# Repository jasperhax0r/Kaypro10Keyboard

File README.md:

# Kaypro 10 Replacement Keyboard

A modern replacement keyboard for the Kaypro 10 that fits the original case, using Cherry MX-style switches and a Raspberry Pi Pico running MicroPython to emulate the original 300 baud serial keyboard interface.

*KiCad 3D render of the PCB*

*Prototype board installed and working*

---

## Overview

The original Kaypro 10 keyboard is increasingly difficult to find in working condition. This project provides a drop-in replacement that:

- Fits the original Kaypro 10 keyboard case with no modifications
- Uses modern Cherry MX-style mechanical switches
- Communicates over the Kaypro's original 300 baud serial keyboard interface
- Is driven by a Raspberry Pi Pico running MicroPython
- Includes a 3D printed switch support plate (no metal plate in this design)

---

## Repository Contents

All files are in the root of the repository.

| File | Description |
|------|-------------|
| `*.kicad_pro`, `*.kicad_sch`, `*.kicad_pcb`, etc. | KiCad 10 schematic and PCB design files |
| `KayproKeyboard.zip` | Generated Gerber/manufacturing files, ready to send to a PCB fab |
| `KayproKeyboard.png` | KiCad 3D render of the board |
| `keyboard support.stl` | 3D printable switch support plate |
| `main.py` | MicroPython firmware for the Raspberry Pi Pico |
| `PXL_20260531_222427528.jpg` | Photo of the working prototype |

---

## Bill of Materials

| Qty | Component | Notes |
|-----|-----------|-------|
| 76 | 1N4148 diode | One per switch, for key matrix decoding |
| 76 | Cherry MX-style switches | One per key position |
| — | PCB-mount stabilizers | Required for larger keys (spacebar, shift, enter, etc.) — quantity depends on layout |
| 1 | Waveshare BS138 4-channel bidirectional level shifter module | 3.3V ↔ 5V logic level conversion |
| 1 | Passive buzzer/speaker | Key click feedback |
| 1 | LED (single, any color) | Status indicator |
| 1 | 330Ω resistor | LED current limiting |
| 1 | 47kΩ resistor | Pull-up/pull-down for serial line |
| 1 | Protection diode | 5V input protection for the Pico |
| 1 | Raspberry Pi Pico | Main controller (standard Pico, not Pico W) |
| 1 | 6-pin horizontal header | Serial interface connector to Kaypro mainboard |

> **Note:** Use 1N4148 diodes (or equivalent) for the key matrix. One diode is required per switch to prevent ghosting.

---

## PCB Manufacturing

The file `KayproKeyboard.zip` contains all Gerber files needed for fabrication. It can be uploaded directly to most PCB manufacturers (JLCPCB, PCBWay, OSHPark, etc.) without modification.

Recommended specs:
- **Layers:** 2
- **Thickness:** 1.6mm
- **Surface finish:** HASL or ENIG

---

## 3D Printed Support

Because this design does not use a metal switch plate, a 3D printed support structure (`keyboard support.stl`) is included to provide rigidity and hold the switches in alignment during soldering and use.

Print in PLA or PETG at 0.2mm layer height with at least 20% infill. No supports should be needed.

---

## Firmware

The Pico runs MicroPython. Copy `main.py` to the Pico's root filesystem and it will start automatically on boot.

### Flashing the Pico

1. Hold the BOOTSEL button and connect the Pico to your computer via USB.
2. It will appear as a USB mass storage device (`RPI-RP2`).
3. Flash the latest [MicroPython UF2](https://micropython.org/download/rp2-pico/) by dragging it onto the drive.
4. Once rebooted, use a tool like [Thonny](https://thonny.org/) or `mpremote` to copy `main.py` to the Pico:
   ```
   mpremote cp main.py :main.py
   ```

The firmware reads the key matrix, debounces inputs, and outputs the correct character codes over the serial interface at 300 baud to match the Kaypro's original keyboard protocol.

---

## Connector Pinout

The keyboard connects to the Kaypro 10 mainboard via a 6-pin horizontal header. Pinout, numbered left to right:

| Pin | Signal | Description |
|-----|--------|-------------|
| 1 | 5V | Power from Kaypro mainboard |
| 2 | TX | Serial data out — keyboard → Kaypro, 300 baud |
| 3 | GND | Ground |
| 4 | GND | Ground |
| 5 | — | Missing/keyed pin (no connection) |
| 6 | RX | Serial data in — Kaypro → keyboard, 300 baud |

> ⚠️ **Important:** This pinout was determined from an **1983-spec Kaypro 10**. It may not be universal across all Kaypro models or revisions. Verify against your own machine before connecting. The protection diode on the 5V input and the BS138 level shifter are strongly recommended to avoid damaging the Pico.

The BS138 level shifter module handles 3.3V Pico ↔ 5V Kaypro logic translation on the TX and RX lines.

---

## Design Files

Schematics and PCB layout were created in **KiCad 10**. The KiCad project files are in the root directory and can be opened and modified freely.

---

## License

This project is open source. Schematics, PCB files, firmware, and mechanical files are provided as-is for personal and educational use.

Contributions, improvements, and ports to other Kaypro models are welcome — open a PR or issue!

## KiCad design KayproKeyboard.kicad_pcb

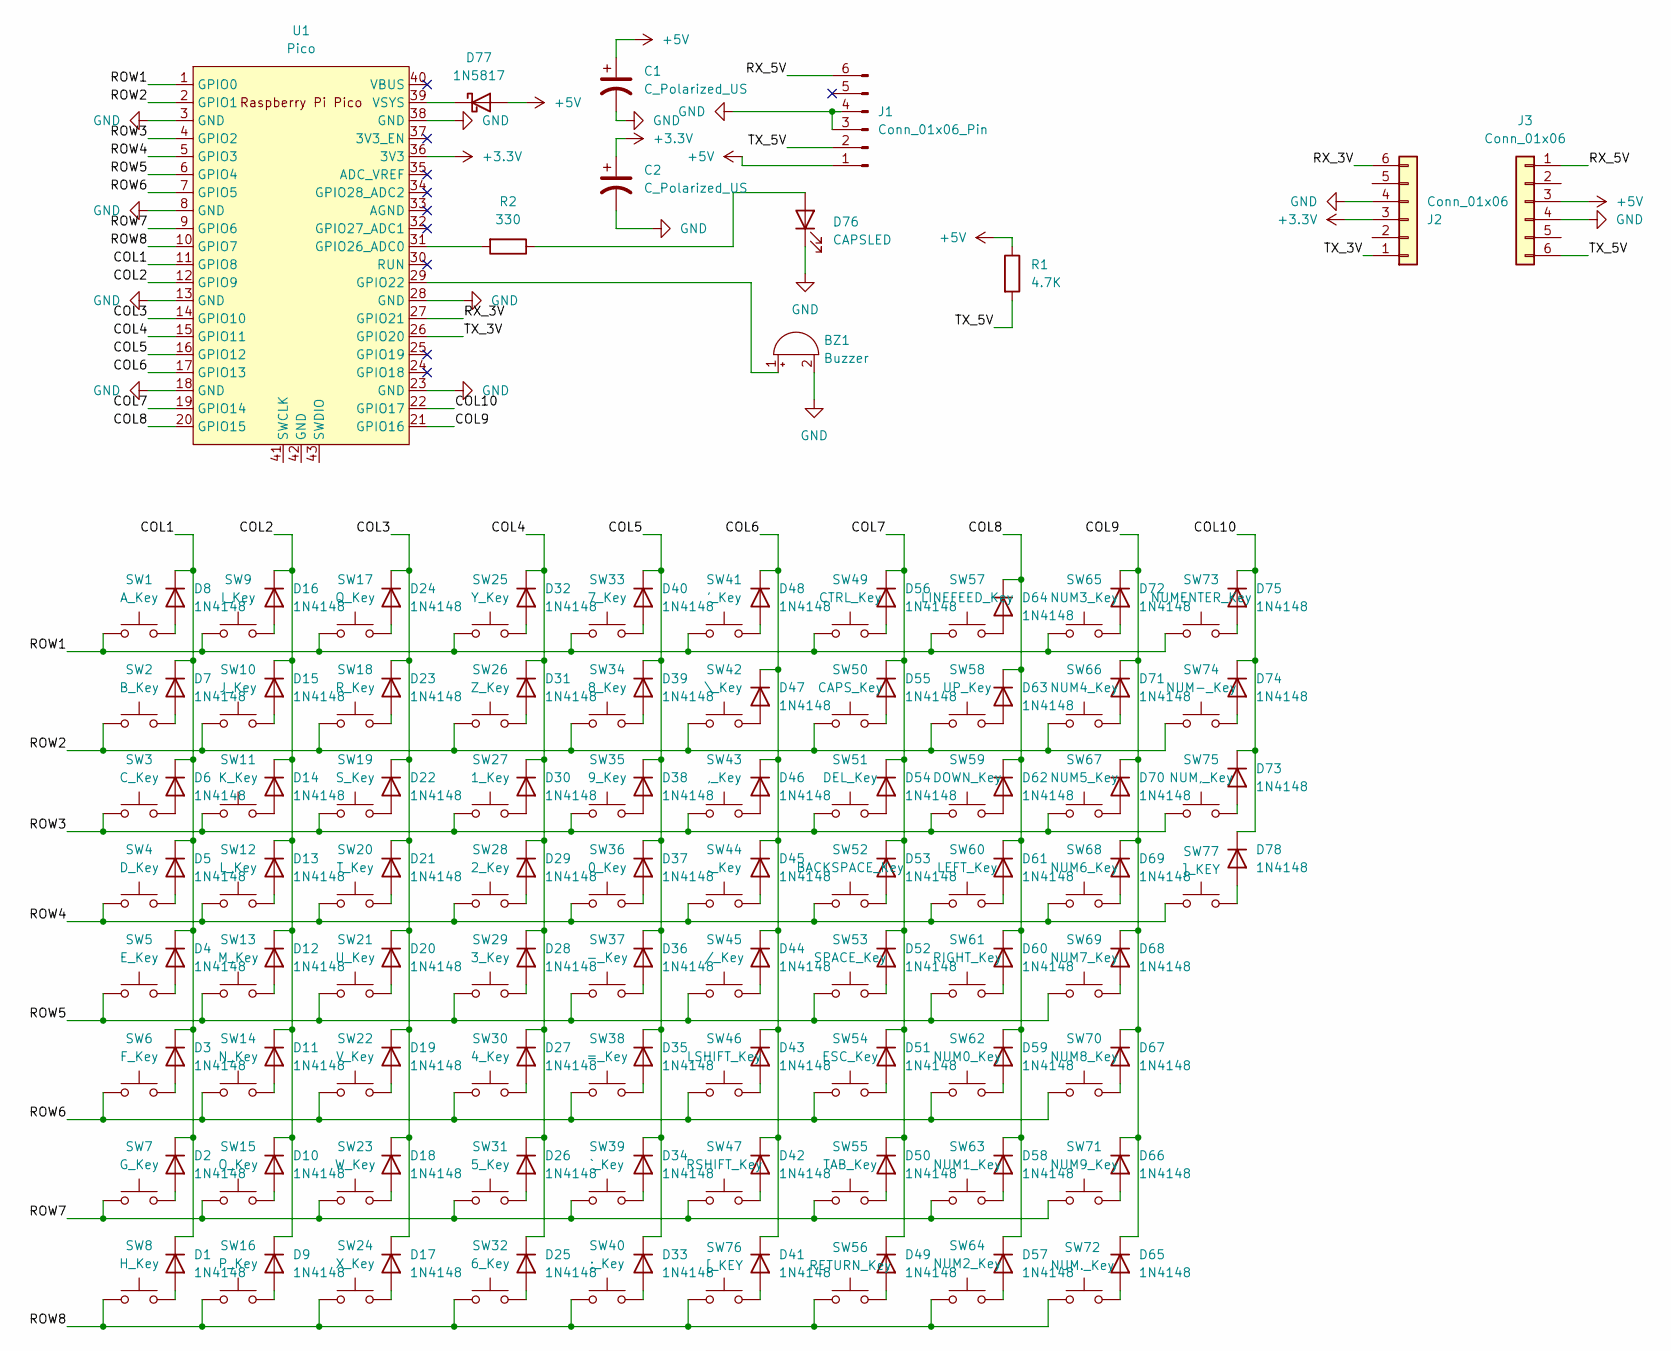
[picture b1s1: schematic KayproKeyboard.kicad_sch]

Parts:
BZ1: Buzzer; Buzzer_12x9.5RM7.6
C1, C2: C_Polarized_US; CP_Radial_D6.3mm_P2.50mm
D1, D2, D3, D4, D5, D6, D7, D8, D9, D10, D11, D12, D13, D14, D15, D16, D17, D18, D19, D20, D21, D22, D23, D24, D25, D26, D27, D28, D29, D30, D31, D32, D33, D34, D35, D36, D37, D38, D39, D40, D41, D42, D43, D44, D45, D46, D47, D48, D49, D50, D51, D52, D53, D54, D55, D56, D57, D58, D59, D60, D61, D62, D63, D64, D65, D66, D67, D68, D69, D70, D71, D72, D73, D74, D75, D78: 1N4148; D_DO-35_SOD27_P7.62mm_Horizontal
D76: CAPSLED; LED_D1.8mm_W1.8mm_H2.4mm_Horizontal_O1.27mm_Z4.9mm
D77: 1N5817; D_DO-41_SOD81_P10.16mm_Horizontal
J1: Conn_01x06_Pin; PinHeader_1x06_P2.54mm_Horizontal
J2, J3: Conn_01x06; 1x06_P2.54mm
R1: 4.7K; R_Axial_DIN0204_L3.6mm_D1.6mm_P7.62mm_Horizontal
R2: 330; R_Axial_DIN0204_L3.6mm_D1.6mm_P7.62mm_Horizontal
SW1: A_Key; SW_Cherry_MX_1.00u_PCB
SW2: B_Key; SW_Cherry_MX_1.00u_PCB
SW3: C_Key; SW_Cherry_MX_1.00u_PCB
SW4: D_Key; SW_Cherry_MX_1.00u_PCB
SW5: E_Key; SW_Cherry_MX_1.00u_PCB
SW6: F_Key; SW_Cherry_MX_1.00u_PCB
SW7: G_Key; SW_Cherry_MX_1.00u_PCB
SW8: H_Key; SW_Cherry_MX_1.00u_PCB
SW9: I_Key; SW_Cherry_MX_1.00u_PCB
SW10: J_Key; SW_Cherry_MX_1.00u_PCB
SW11: K_Key; SW_Cherry_MX_1.00u_PCB
SW12: L_Key; SW_Cherry_MX_1.00u_PCB
SW13: M_Key; SW_Cherry_MX_1.00u_PCB
SW14: N_Key; SW_Cherry_MX_1.00u_PCB
SW15: O_Key; SW_Cherry_MX_1.00u_PCB
SW16: P_Key; SW_Cherry_MX_1.00u_PCB
SW17: Q_Key; SW_Cherry_MX_1.00u_PCB
SW18: R_Key; SW_Cherry_MX_1.00u_PCB
SW19: S_Key; SW_Cherry_MX_1.00u_PCB
SW20: T_Key; SW_Cherry_MX_1.00u_PCB
SW21: U_Key; SW_Cherry_MX_1.00u_PCB
SW22: V_Key; SW_Cherry_MX_1.00u_PCB
SW23: W_Key; SW_Cherry_MX_1.00u_PCB
SW24: X_Key; SW_Cherry_MX_1.00u_PCB
SW25: Y_Key; SW_Cherry_MX_1.00u_PCB
SW26: Z_Key; SW_Cherry_MX_1.00u_PCB
SW27: 1_Key; SW_Cherry_MX_1.00u_PCB
SW28: 2_Key; SW_Cherry_MX_1.00u_PCB
SW29: 3_Key; SW_Cherry_MX_1.00u_PCB
SW30: 4_Key; SW_Cherry_MX_1.00u_PCB
SW31: 5_Key; SW_Cherry_MX_1.00u_PCB
SW32: 6_Key; SW_Cherry_MX_1.00u_PCB
SW33: 7_Key; SW_Cherry_MX_1.00u_PCB
SW34: 8_Key; SW_Cherry_MX_1.00u_PCB
SW35: 9_Key; SW_Cherry_MX_1.00u_PCB
SW36: 0_Key; SW_Cherry_MX_1.00u_PCB
SW37: -_Key; SW_Cherry_MX_1.00u_PCB
SW38: =_Key; SW_Cherry_MX_1.00u_PCB
SW39: `_Key; SW_Cherry_MX_1.00u_PCB
SW40: ;_Key; SW_Cherry_MX_1.00u_PCB
SW41: '_Key; SW_Cherry_MX_1.00u_PCB
SW42: \_Key; SW_Cherry_MX_1.00u_PCB
SW43: ,_Key; SW_Cherry_MX_1.00u_PCB
SW44: ._Key; SW_Cherry_MX_1.00u_PCB
SW45: /_Key; SW_Cherry_MX_1.00u_PCB
SW46: LSHIFT_Key; SW_Cherry_MX_2.00u_PCB
SW47: RSHIFT_Key; SW_Cherry_MX_2.00u_PCB
SW49: CTRL_Key; SW_Cherry_MX_1.00u_PCB
SW50: CAPS_Key; SW_Cherry_MX_1.75u_PCB
SW51: DEL_Key; SW_Cherry_MX_1.00u_PCB
SW52: BACKSPACE_Key; SW_Cherry_MX_1.00u_PCB
SW53: SPACE_Key; SW_Cherry_MX_6.25u_PCB
SW54: ESC_Key; SW_Cherry_MX_1.00u_PCB
SW55: TAB_Key; SW_Cherry_MX_1.75u_PCB
SW56: RETURN_Key; SW_Cherry_MX_1.50u_PCB
SW57: LINEFEED_Key; SW_Cherry_MX_1.00u_PCB
SW58: UP_Key; SW_Cherry_MX_1.00u_PCB
SW59: DOWN_Key; SW_Cherry_MX_1.00u_PCB
SW60: LEFT_Key; SW_Cherry_MX_1.00u_PCB
SW61: RIGHT_Key; SW_Cherry_MX_1.00u_PCB
SW62: NUM0_Key; SW_Cherry_MX_2.00u_PCB
SW63: NUM1_Key; SW_Cherry_MX_1.00u_PCB
SW64: NUM2_Key; SW_Cherry_MX_1.00u_PCB
SW65: NUM3_Key; SW_Cherry_MX_1.00u_PCB
SW66: NUM4_Key; SW_Cherry_MX_1.00u_PCB
SW67: NUM5_Key; SW_Cherry_MX_1.00u_PCB
SW68: NUM6_Key; SW_Cherry_MX_1.00u_PCB
SW69: NUM7_Key; SW_Cherry_MX_1.00u_PCB
SW70: NUM8_Key; SW_Cherry_MX_1.00u_PCB
SW71: NUM9_Key; SW_Cherry_MX_1.00u_PCB
SW72: NUM._Key; SW_Cherry_MX_1.00u_PCB
SW73: NUMENTER_Key; SW_Cherry_MX_2.00u_Vertical_PCB
SW74: NUM-_Key; SW_Cherry_MX_1.00u_PCB
SW75: NUM,_Key; SW_Cherry_MX_1.00u_PCB
SW76: [_KEY; SW_Cherry_MX_1.00u_PCB
SW77: ]_KEY; SW_Cherry_MX_1.00u_PCB
U1: Pico; RPi_Pico_SMD_TH

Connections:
+3.3V: C2.1, J2.3, U1.36 (3V3)
+5V: C1.1, D77.2 (A), J1.1, J3.3, R1.1
/COL1: D1.1 (K), D2.1 (K), D3.1 (K), D4.1 (K), D5.1 (K), D6.1 (K), D7.1 (K), D8.1 (K), U1.11 (GPIO8)
/COL2: D9.1 (K), D10.1 (K), D11.1 (K), D12.1 (K), D13.1 (K), D14.1 (K), D15.1 (K), D16.1 (K), U1.12 (GPIO9)
/COL3: D17.1 (K), D18.1 (K), D19.1 (K), D20.1 (K), D21.1 (K), D22.1 (K), D23.1 (K), D24.1 (K), U1.14 (GPIO10)
/COL4: D25.1 (K), D26.1 (K), D27.1 (K), D28.1 (K), D29.1 (K), D30.1 (K), D31.1 (K), D32.1 (K), U1.15 (GPIO11)
/COL5: D33.1 (K), D34.1 (K), D35.1 (K), D36.1 (K), D37.1 (K), D38.1 (K), D39.1 (K), D40.1 (K), U1.16 (GPIO12)
/COL6: D41.1 (K), D42.1 (K), D43.1 (K), D44.1 (K), D45.1 (K), D46.1 (K), D47.1 (K), D48.1 (K), U1.17 (GPIO13)
/COL7: D49.1 (K), D50.1 (K), D51.1 (K), D52.1 (K), D53.1 (K), D54.1 (K), D55.1 (K), D56.1 (K), U1.19 (GPIO14)
/COL8: D57.1 (K), D58.1 (K), D59.1 (K), D60.1 (K), D61.1 (K), D62.1 (K), D63.1 (K), D64.1 (K), U1.20 (GPIO15)
/COL9: D65.1 (K), D66.1 (K), D67.1 (K), D68.1 (K), D69.1 (K), D70.1 (K), D71.1 (K), D72.1 (K), U1.21 (GPIO16)
/COL10: D73.1 (K), D74.1 (K), D75.1 (K), D78.1 (K), U1.22 (GPIO17)
/ROW1: SW1.1, SW9.1, SW17.1, SW25.1, SW33.1, SW41.1, SW49.1, SW57.1, SW65.1, SW73.1, U1.1 (GPIO0)
/ROW2: SW2.1, SW10.1, SW18.1, SW26.1, SW34.1, SW42.1, SW50.1, SW58.1, SW66.1, SW74.1, U1.2 (GPIO1)
/ROW3: SW3.1, SW11.1, SW19.1, SW27.1, SW35.1, SW43.1, SW51.1, SW59.1, SW67.1, SW75.1, U1.4 (GPIO2)
/ROW4: SW4.1, SW12.1, SW20.1, SW28.1, SW36.1, SW44.1, SW52.1, SW60.1, SW68.1, SW77.1, U1.5 (GPIO3)
/ROW5: SW5.1, SW13.1, SW21.1, SW29.1, SW37.1, SW45.1, SW53.1, SW61.1, SW69.1, U1.6 (GPIO4)
/ROW6: SW6.1, SW14.1, SW22.1, SW30.1, SW38.1, SW46.1, SW54.1, SW62.1, SW70.1, U1.7 (GPIO5)
/ROW7: SW7.1, SW15.1, SW23.1, SW31.1, SW39.1, SW47.1, SW55.1, SW63.1, SW71.1, U1.9 (GPIO6)
/ROW8: SW8.1, SW16.1, SW24.1, SW32.1, SW40.1, SW56.1, SW64.1, SW72.1, SW76.1, U1.10 (GPIO7)
/RX_3V: J2.6, U1.27 (GPIO21)
/RX_5V: J1.6, J3.1
/TX_3V: J2.1, U1.26 (GPIO20)
/TX_5V: J1.2, J3.6, R1.2
GND: BZ1.2 (-), C1.2, C2.2, D76.1 (K), J1.3, J1.4, J2.4, J3.4, U1.3 (GND), U1.8 (GND), U1.13 (GND), U1.18 (GND), U1.23 (GND), U1.28 (GND), U1.38 (GND)
unnamed: BZ1.1 (+), U1.29 (GPIO22)
unnamed: D1.2 (A), SW8.2
unnamed: D2.2 (A), SW7.2
unnamed: D3.2 (A), SW6.2
unnamed: D4.2 (A), SW5.2
unnamed: D5.2 (A), SW4.2
unnamed: D6.2 (A), SW3.2
unnamed: D7.2 (A), SW2.2
unnamed: D8.2 (A), SW1.2
unnamed: D9.2 (A), SW16.2
unnamed: D10.2 (A), SW15.2
unnamed: D11.2 (A), SW14.2
unnamed: D12.2 (A), SW13.2
unnamed: D13.2 (A), SW12.2
unnamed: D14.2 (A), SW11.2
unnamed: D15.2 (A), SW10.2
unnamed: D16.2 (A), SW9.2
unnamed: D17.2 (A), SW24.2
unnamed: D18.2 (A), SW23.2
unnamed: D19.2 (A), SW22.2
unnamed: D20.2 (A), SW21.2
unnamed: D21.2 (A), SW20.2
unnamed: D22.2 (A), SW19.2
unnamed: D23.2 (A), SW18.2
unnamed: D24.2 (A), SW17.2
unnamed: D25.2 (A), SW32.2
unnamed: D26.2 (A), SW31.2
unnamed: D27.2 (A), SW30.2
unnamed: D28.2 (A), SW29.2
unnamed: D29.2 (A), SW28.2
unnamed: D30.2 (A), SW27.2
unnamed: D31.2 (A), SW26.2
unnamed: D32.2 (A), SW25.2
unnamed: D33.2 (A), SW40.2
unnamed: D34.2 (A), SW39.2
unnamed: D35.2 (A), SW38.2
unnamed: D36.2 (A), SW37.2
unnamed: D37.2 (A), SW36.2
unnamed: D38.2 (A), SW35.2
unnamed: D39.2 (A), SW34.2
unnamed: D40.2 (A), SW33.2
unnamed: D41.2 (A), SW76.2
unnamed: D42.2 (A), SW47.2
unnamed: D43.2 (A), SW46.2
unnamed: D44.2 (A), SW45.2
unnamed: D45.2 (A), SW44.2
unnamed: D46.2 (A), SW43.2
unnamed: D47.2 (A), SW42.2
unnamed: D48.2 (A), SW41.2
unnamed: D49.2 (A), SW56.2
unnamed: D50.2 (A), SW55.2
unnamed: D51.2 (A), SW54.2
unnamed: D52.2 (A), SW53.2
unnamed: D53.2 (A), SW52.2
unnamed: D54.2 (A), SW51.2
unnamed: D55.2 (A), SW50.2
unnamed: D56.2 (A), SW49.2
unnamed: D57.2 (A), SW64.2
unnamed: D58.2 (A), SW63.2
unnamed: D59.2 (A), SW62.2
unnamed: D60.2 (A), SW61.2
unnamed: D61.2 (A), SW60.2
unnamed: D62.2 (A), SW59.2
unnamed: D63.2 (A), SW58.2
unnamed: D64.2 (A), SW57.2
unnamed: D65.2 (A), SW72.2
unnamed: D66.2 (A), SW71.2
unnamed: D67.2 (A), SW70.2
unnamed: D68.2 (A), SW69.2
unnamed: D69.2 (A), SW68.2
unnamed: D70.2 (A), SW67.2
unnamed: D71.2 (A), SW66.2
unnamed: D72.2 (A), SW65.2
unnamed: D73.2 (A), SW75.2
unnamed: D74.2 (A), SW74.2
unnamed: D75.2 (A), SW73.2
unnamed: D76.2 (A), R2.1
unnamed: D77.1 (K), U1.39 (VSYS)
unnamed: D78.2 (A), SW77.2
unnamed: R2.2, U1.31 (GPIO26_ADC0)

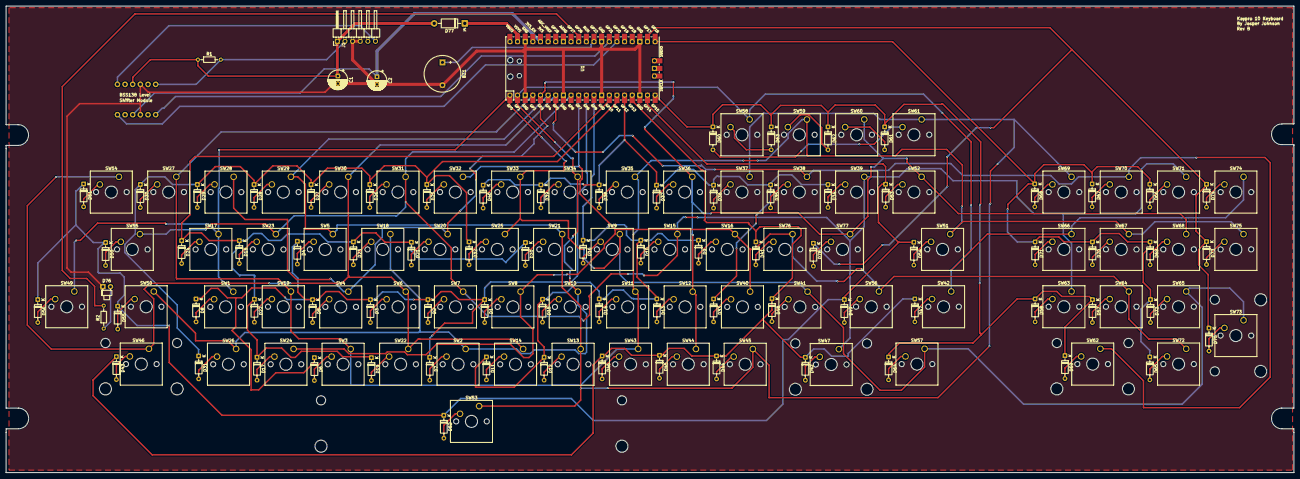
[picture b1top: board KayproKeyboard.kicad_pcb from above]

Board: 2 copper layers, 427.9 x 155.0 mm, 163 parts (0 on the bottom side), 105 nets.

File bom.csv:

Designator,Footprint,Quantity,Value,LCSC Part #
BZ1,Buzzer_12x9.5RM7.6,1,Buzzer,
"C1, C2",CP_Radial_D6.3mm_P2.50mm,2,C_Polarized_US,
"D1, D10, D11, D12, D13, D14, D15, D16, D17, D18, D19, D2, D20, D21, D22, D23, D24, D25, D26, D27, D28, D29, D3, D30, D31, D32, D33, D34, D35, D36, D37, D38, D39, D4, D40, D41, D42, D43, D44, D45, D46, D47, D48, D49, D5, D50, D51, D52, D53, D54, D55, D56, D57, D58, D59, D6, D60, D61, D62, D63, D64, D65, D66, D67, D68, D69, D7, D70, D71, D72, D73, D74, D75, D78, D8, D9",D_DO-35_SOD27_P7.62mm_Horizontal,76,1N4148,
D76,LED_D1.8mm_W1.8mm_H2.4mm_Horizontal_O1.27mm_Z4.9mm,1,CAPSLED,
D77,D_DO-41_SOD81_P10.16mm_Horizontal,1,1N5817,
J1,PinHeader_1x06_P2.54mm_Horizontal,1,Conn_01x06_Pin,
"J2, J3",1x06_P2.54mm,2,Conn_01x06,
R1,R_Axial_DIN0204_L3.6mm_D1.6mm_P7.62mm_Horizontal,1,4.7K,
R2,R_Axial_DIN0204_L3.6mm_D1.6mm_P7.62mm_Horizontal,1,330,
SW1,SW_Cherry_MX_1.00u_PCB,1,A_Key,
SW10,SW_Cherry_MX_1.00u_PCB,1,J_Key,
SW11,SW_Cherry_MX_1.00u_PCB,1,K_Key,
SW12,SW_Cherry_MX_1.00u_PCB,1,L_Key,
SW13,SW_Cherry_MX_1.00u_PCB,1,M_Key,
SW14,SW_Cherry_MX_1.00u_PCB,1,N_Key,
SW15,SW_Cherry_MX_1.00u_PCB,1,O_Key,
SW16,SW_Cherry_MX_1.00u_PCB,1,P_Key,
SW17,SW_Cherry_MX_1.00u_PCB,1,Q_Key,
SW18,SW_Cherry_MX_1.00u_PCB,1,R_Key,
SW19,SW_Cherry_MX_1.00u_PCB,1,S_Key,
SW2,SW_Cherry_MX_1.00u_PCB,1,B_Key,
SW20,SW_Cherry_MX_1.00u_PCB,1,T_Key,
SW21,SW_Cherry_MX_1.00u_PCB,1,U_Key,
SW22,SW_Cherry_MX_1.00u_PCB,1,V_Key,
SW23,SW_Cherry_MX_1.00u_PCB,1,W_Key,
SW24,SW_Cherry_MX_1.00u_PCB,1,X_Key,
SW25,SW_Cherry_MX_1.00u_PCB,1,Y_Key,
SW26,SW_Cherry_MX_1.00u_PCB,1,Z_Key,
SW27,SW_Cherry_MX_1.00u_PCB,1,1_Key,
SW28,SW_Cherry_MX_1.00u_PCB,1,2_Key,
SW29,SW_Cherry_MX_1.00u_PCB,1,3_Key,
SW3,SW_Cherry_MX_1.00u_PCB,1,C_Key,
SW30,SW_Cherry_MX_1.00u_PCB,1,4_Key,
SW31,SW_Cherry_MX_1.00u_PCB,1,5_Key,
SW32,SW_Cherry_MX_1.00u_PCB,1,6_Key,
SW33,SW_Cherry_MX_1.00u_PCB,1,7_Key,
SW34,SW_Cherry_MX_1.00u_PCB,1,8_Key,
SW35,SW_Cherry_MX_1.00u_PCB,1,9_Key,
SW36,SW_Cherry_MX_1.00u_PCB,1,0_Key,
SW37,SW_Cherry_MX_1.00u_PCB,1,-_Key,
SW38,SW_Cherry_MX_1.00u_PCB,1,=_Key,
SW39,SW_Cherry_MX_1.00u_PCB,1,`_Key,
SW4,SW_Cherry_MX_1.00u_PCB,1,D_Key,
SW40,SW_Cherry_MX_1.00u_PCB,1,;_Key,
SW41,SW_Cherry_MX_1.00u_PCB,1,'_Key,
SW42,SW_Cherry_MX_1.00u_PCB,1,\_Key,
SW43,SW_Cherry_MX_1.00u_PCB,1,",_Key",
SW44,SW_Cherry_MX_1.00u_PCB,1,._Key,
SW45,SW_Cherry_MX_1.00u_PCB,1,/_Key,
SW46,SW_Cherry_MX_2.00u_PCB,1,LSHIFT_Key,
SW47,SW_Cherry_MX_2.00u_PCB,1,RSHIFT_Key,
SW49,SW_Cherry_MX_1.00u_PCB,1,CTRL_Key,
SW5,SW_Cherry_MX_1.00u_PCB,1,E_Key,
SW50,SW_Cherry_MX_1.75u_PCB,1,CAPS_Key,
SW51,SW_Cherry_MX_1.00u_PCB,1,DEL_Key,
SW52,SW_Cherry_MX_1.00u_PCB,1,BACKSPACE_Key,
SW53,SW_Cherry_MX_6.25u_PCB,1,SPACE_Key,
SW54,SW_Cherry_MX_1.00u_PCB,1,ESC_Key,
SW55,SW_Cherry_MX_1.75u_PCB,1,TAB_Key,
SW56,SW_Cherry_MX_1.50u_PCB,1,RETURN_Key,
SW57,SW_Cherry_MX_1.00u_PCB,1,LINEFEED_Key,
SW58,SW_Cherry_MX_1.00u_PCB,1,UP_Key,
SW59,SW_Cherry_MX_1.00u_PCB,1,DOWN_Key,
SW6,SW_Cherry_MX_1.00u_PCB,1,F_Key,
SW60,SW_Cherry_MX_1.00u_PCB,1,LEFT_Key,
SW61,SW_Cherry_MX_1.00u_PCB,1,RIGHT_Key,
SW62,SW_Cherry_MX_2.00u_PCB,1,NUM0_Key,
SW63,SW_Cherry_MX_1.00u_PCB,1,NUM1_Key,
SW64,SW_Cherry_MX_1.00u_PCB,1,NUM2_Key,
SW65,SW_Cherry_MX_1.00u_PCB,1,NUM3_Key,
SW66,SW_Cherry_MX_1.00u_PCB,1,NUM4_Key,
SW67,SW_Cherry_MX_1.00u_PCB,1,NUM5_Key,
SW68,SW_Cherry_MX_1.00u_PCB,1,NUM6_Key,
SW69,SW_Cherry_MX_1.00u_PCB,1,NUM7_Key,
SW7,SW_Cherry_MX_1.00u_PCB,1,G_Key,
SW70,SW_Cherry_MX_1.00u_PCB,1,NUM8_Key,
SW71,SW_Cherry_MX_1.00u_PCB,1,NUM9_Key,
SW72,SW_Cherry_MX_1.00u_PCB,1,NUM._Key,
SW73,SW_Cherry_MX_2.00u_Vertical_PCB,1,NUMENTER_Key,
SW74,SW_Cherry_MX_1.00u_PCB,1,NUM-_Key,
SW75,SW_Cherry_MX_1.00u_PCB,1,"NUM,_Key",
SW76,SW_Cherry_MX_1.00u_PCB,1,[_KEY,
SW77,SW_Cherry_MX_1.00u_PCB,1,]_KEY,
SW8,SW_Cherry_MX_1.00u_PCB,1,H_Key,
SW9,SW_Cherry_MX_1.00u_PCB,1,I_Key,
U1,RPi_Pico_SMD_TH,1,Pico,

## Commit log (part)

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2026-06-02 Uploaded initial files
